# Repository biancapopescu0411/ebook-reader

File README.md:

# README - OpenBook

**OpenBook** este un sistem portabil pentru citirea cărților electronice, proiectat în jurul microcontrollerului ESP32-C6-WROOM-1-N8. Dispozitivul integrează o serie de componente inteligente pentru stocare, afișare, alimentare și comunicații, toate optimizate pentru eficiență energetică și portabilitate.

## Diagrama bloc

---

## Componente Hardware & Funcționalitate
### Microcontroller Principal
- **ESP32-C6-WROOM-1-N8**

- Procesor RISC-V 32-bit

- Conectivitate Wi-Fi 6 și Bluetooth 5.0

- Memorie Flash internă de 8MB

- Nivel logic și alimentare: 3.3V

- Responsabil de comunicarea cu senzorii, ecranul EPD, memoria externă și stocarea datelor.

---

## Interfețe de Comunicație

| Interfață | Componente Conectate |
|----------|-----------------------|
| **I2C**  | BME688, MAX17048, DS3231SN |
| **SPI**  | Display E-Ink, SD Card, Flash Memory |
| **UART** | Serial debug via USB-C (TX/RX) |
| **GPIO** | Butoane, LED-uri, semnale control |

---

## Energie și Alimentare

- Alimentare prin **USB-C** sau baterie **Li-Po**
- Condensatori de decuplare de **100nF** aproape de fiecare pin de alimentare
- Regulator **LDO 3.3V** pentru circuitele logice
- Încărcarea bateriei este gestionată de **MCP73831**
- Plan de masă aplicat pe ambele straturi (**TOP & BOTTOM**) pentru stabilitate electrică

---

## Funcționalitate Detaliată

### ESP32-C6
- Rol: procesor central, interfațare completă cu toate modulele
- Conectat direct la:
  - UART: comunicare cu e-Paper
  - SPI: display, stocare date
  - I2C: senzori și RTC

### Display E-Ink
- Afișare text/imagine cu consum redus
- Interfață SPI dedicată

### Baterie & Protecții
- Baterie conectată la 4 pad-uri pentru economie de spațiu
- Decuplare prin condensatori de 100nF
- Protecții plasate strategic prin via stitching

---

## Structura Proiect
```
├── Hardware
│   ├── schematic_final.sch            # Fișier schematic
│   └── pcb final.brd            # Fișier PCB
├── Manufacturing
│   ├── gerbers.zip             # Fișiere Gerber generate
│   ├── bom.csv            # Bill of Materials
│   └── Pick and place.csv           # Pick and Place file
├── Mechanical
│   ├── exploded.step  # Model 3D exploded (PCB + baterie + ecran + carcasă)
│   └── OpenBook Enclosure.f3z  # Model nativ Fusion360
├── Images
│   ├── 3d.png
│   └── baterie.png
|   └── exploded view.png
|   └── no lid.png
|   └── openbook enclosure.png
|   └── screen view.png
|   └── screen.png
└── README.md
```

## Bill of Materials
| Componenta | Link | Datasheet |
|-----------|--------------|-----------|
| BUTTON | [Model](https://industry.panasonic.com/global/en/products/control/switch/light-touch/number/evqpuj02k) | [Datasheet](https://www.lcsc.com/datasheet/lcsc_datasheet_2201121800_PANASONIC-EVQPUJ02K_C2936858.pdf) |
| CAPACITOR | [Model](https://componentsearchengine.com/part-view/R0402%201%25%20100%20K%20(RC0402FR-07100KL)/YAGEO) | [Datasheet](//efaidnbmnnnibpcajpcglclefindmkaj/https://www.resistor.com/assets/pdf/0402tstd.pdf) |
| CPH3225A | [Model](https://www.snapeda.com/parts/CPH3225A/Seiko+Instruments/view-part/?ref=eda) | [Datasheet](https://octopart.com/datasheet/cph3225a-seiko-25340571) |
| EVQPUJ02K | [Model](https://industry.panasonic.com/global/en/products/control/switch/light-touch/number/evqpuj02k) | [Datasheet](https://www.lcsc.com/datasheet/lcsc_datasheet_2201121800_PANASONIC-EVQPUJ02K_C2936858.pdf) |
| KP-1608SURCK | [Model](https://www.snapeda.com/parts/KP-1608SURCK/Kingbright/view-part/?ref=search&t=LED%200603) | [Datasheet](//efaidnbmnnnibpcajpcglclefindmkaj/https://media.elv.com/file/107153_led_surck1608_data.pdf) |
| USBLC6-2SC6Y | [Model](https://www.snapeda.com/parts/USBLC6-2SC6Y/STMicroelectronics/view-part/?ref=eda) | [Datasheet](https://www.digikey.com/en/htmldatasheets/production/1375342/0/0/1/usblc6-2sc6y) |
| SD0805S020S1R0 | [Model](https://ro.mouser.com/ProductDetail/KYOCERA-AVX/SD0805S020S1R0?qs=jCA%252BPfw4LHbpkAoSnwrdjw%3D%3D) | [Datasheet](https://www.alldatasheet.com/view.jsp?Searchword=SD0805S&sField=2) |
| PGB1010603MR | [Model](https://www.snapeda.com/parts/PGB1010603MR/Littelfuse/view-part/?ref=eda) | [Datasheet](https://www.alldatasheet.com/view.jsp?Searchword=Pgb1010603mr&gad_source=1&gbraid=0AAAAADcdDU8aYfZtfJfdZ9I5j6RwZ_cbA&gclid=Cj0KCQjwqcO_BhDaARIsACz62vOPBOBe0eOh5gDUFkkKl4JBcbmoFZYtJ8BOnbaWqr_BuUCcVWvbutAaAmGkEALw_wcB) |
| BD5229G-TR  | [Model](https://componentsearchengine.com/part-view/BD5229G-TR/ROHM%20Semiconductor) | [Datasheet](https://www.lcsc.com/datasheet/lcsc_datasheet_2201131330_ROHM-Semicon-BD5229G-TR_C962636.pdf) |
| XC6220A331MR-G | [Model](https://componentsearchengine.com/part-view/XC6220A331MR-G/Torex) | [Datasheet](https://www.alldatasheet.com/view.jsp?Searchword=Xc6220&gad_source=1&gbraid=0AAAAADcdDU8aYfZtfJfdZ9I5j6RwZ_cbA&gclid=Cj0KCQjwqcO_BhDaARIsACz62vPS06NB6tLgniZzfaVpKNu1m811BNk6AEPfg4DbP6f5S8QWA_pW_UQaAv-0EALw_wcB) |
| XC6220A331MR-G | [Model](https://componentsearchengine.com/part-view/XC6220A331MR-G/Torex) | [Datasheet](https://www.alldatasheet.com/view.jsp?Searchword=Xc6220&gad_source=1&gbraid=0AAAAADcdDU8aYfZtfJfdZ9I5j6RwZ_cbA&gclid=Cj0KCQjwqcO_BhDaARIsACz62vMO5_aHsn35cIZBK6oCFuB_WOxz_zKu4yOHJ69-EnaUd5Jfas_Avm8aAuk5EALw_wcB) |
| USB4110-GF-A  | [Model](https://componentsearchengine.com/part-view/USB4110-GF-A/GCT%20(GLOBAL%20CONNECTOR%20TECHNOLOGY)) | [Datasheet](//efaidnbmnnnibpcajpcglclefindmkaj/https://gct.co/files/drawings/usb4110.pdf) |
| Adafruit | [Model](https://eu.mouser.com/ProductDetail/Adafruit/4208?qs=PzGy0jfpSMtbScLbr0L5dw%3D%3D) | [Datasheet](https://www.arrow.com/en/manufacturers/adafruit-industries/datasheets) |
| Bobina | [Model](https://store.comet.srl.ro/Catalogue/Product/43497/) | [Datasheet](https://www.scribd.com/document/814581278/Datasheet-Bobina) |
| PFMF | [Model](https://www.mouser.co.uk/ProductDetail/EPCOS-TDK/B72520T0350K062?qs=dEfas%2FXlABIszF52uu7vrg%3D%3D) | [Datasheet](https://ro.mouser.com/c/ds/circuit-protection/thermistors/resettable-fuses-pptc/?m=Schurter&series=PFMF) |
| DMG2305UX-7 | [Model](https://componentsearchengine.com/part-view/DMG2305UX-7/Diodes%20Incorporated) | [Datasheet](//efaidnbmnnnibpcajpcglclefindmkaj/https://www.mouser.com/datasheet/2/115/DMG2305UX-266242.pdf?srsltid=AfmBOop22k34YTJJra1xubiU6LPiN4M4JlcWbRoSNdxSGFak8uWgXPpK) |
| Si1308EDL-T1-GE3 | [Model](https://componentsearchengine.com/part-view/SI1308EDL-T1-GE3/Vishay) | [Datasheet](https://www.alldatasheet.com/view.jsp?Searchword=Si1308edl&gad_source=1&gbraid=0AAAAADcdDU-px713ONYSnQ2O-gcwqYcFq&gclid=Cj0KCQjwqcO_BhDaARIsACz62vN_Nz3MJOc6J_03gnVBm7aSqC8v9wyP0VD-iRKP-gFrYgdhLi99I14aAlVJEALw_wcB) |
| R0402 | [Model](https://componentsearchengine.com/part-view/R0402%201%25%20100%20K%20(RC0402FR-07100KL)/YAGEO) | [Datasheet](//efaidnbmnnnibpcajpcglclefindmkaj/https://www.resistor.com/assets/pdf/0402tstd.pdf) |
| BME680 | [Model](https://www.snapeda.com/parts/BME680/Bosch/view-part/?welcome=home) | [Datasheet](//efaidnbmnnnibpcajpcglclefindmkaj/https://www.bosch-sensortec.com/media/boschsensortec/downloads/datasheets/bst-bme680-ds001.pdf) |
| SMD Solder | [Model](https://grabcad.com/library/solder-jumpers-1) | [Datasheet]() |
| W25Q512JVEIQ | [Model](https://www.snapeda.com/parts/ESP32-C6-WROOM-1-N8/Espressif+Systems/view-part/?ref=eda) | [Datasheet](//efaidnbmnnnibpcajpcglclefindmkaj/https://www.mouser.com/datasheet/2/949/W25Q512JV_SPI_RevB_06252019_KMS-2487502.pdf?srsltid=AfmBOoquExqDVgxEELF9CzuOGxHos0CD1nQDROHD6Eebdm2foNzqozqU) |
| ESP32-C6-WROOM-1-N8 | [Model](https://www.snapeda.com/parts/ESP32-C6-WROOM-1-N8/Espressif+Systems/view-part/?ref=eda) | [Datasheet](//efaidnbmnnnibpcajpcglclefindmkaj/https://www.mouser.com/catalog/specsheets/Espressif_ESP32_C6_WROOM_1%20_Datasheet_V0.1_PRELIMINARY_en.pdf?srsltid=AfmBOooHQKNitqODRaaPjoZInfWKTacDER1t5uRK6sKqT13TrzvVo_B7) |
| DS3231SN# | [Model](https://www.snapeda.com/parts/DS3231SN%23/Analog+Devices/view-part/?ref=eda) | [Datasheet](https://www.alldatasheet.com/view.jsp?Searchword=Ds3231sn%20datasheet&gad_source=1&gbraid=0AAAAADcdDU-Gy9URfMxGmqiPg7ci5L3wR&gclid=Cj0KCQjwqcO_BhDaARIsACz62vMkK3ETSnW2w7mo0Fa-wgWJGn89AxWCyIND6k5X8MmoPl6hv6VWwT8aAiS-EALw_wcB) |
| MAX17048G+T10 | [Model](https://www.snapeda.com/parts/MAX17048G+T10/Analog+Devices/view-part/?ref=eda) | [Datasheet](https://www.alldatasheet.com/view.jsp?Searchword=Max17048&gad_source=1&gbraid=0AAAAADcdDU8aYfZtfJfdZ9I5j6RwZ_cbA&gclid=Cj0KCQjwqcO_BhDaARIsACz62vNa9xrVfzjCjADRwXD0RBbo4Nret3ywwteDGLJKZui8ZL8KdVlTE7caAvQxEALw_wcB) |
| MCP73831T-5ACI/OT | [Model](https://www.mouser.co.uk/ProductDetail/Microchip-Technology/MCP73831T-5ACI-OT?qs=hH%252BOa0VZEiAcgAcEkuamXg%3D%3D) | [Datasheet](//efaidnbmnnnibpcajpcglclefindmkaj/https://ww1.microchip.com/downloads/en/DeviceDoc/MCP73831-Family-Data-Sheet-DS20001984H.pdf) |

## Detaliere Pini Utilizați (ESP32-C6 / U2)

| Pin ESP32 | Funcție Principală                  | Componentă Conectată / Scop                  |
| :-------- | :---------------------------------- | :------------------------------------------- |
| IO3       | RESET                               | SW2, IC5                                     |
| IO5       | GPIO                                | J4 (EPD_DC)                                  |
| IO6       | SPI SCK                             | J4 (EPD_SCK), J3 (SD_CLK)                    |
| IO7       | SPI MOSI                            | J4 (EPD_DIN), J3 (SD_DI)                     |
| IO8       | BOOT                                | SW1 (Buton Boot)                             |
| IO10      | GPIO / SPI CS                       | J3 (SD_CS)                                   |
| IO11      | GPIO / SPI CS                       | J4 (EPD_CS)                                  |
| IO13      | USB D-                              | J2 (USB-C D-) via D2                         |
| IO14      | USB D+                              | J2 (USB-C D+) via D2                         |
| IO19      | I2C SDA                             | IC2 (RTC SDA), IC3 (BME SDA/SDO)             |
| IO20      | I2C SCL                             | IC2 (RTC SCL), IC3 (BME SCL/SCK)             |
| IO21      | GPIO                                | J4 (EPD_RST)                                 |
| IO26      | GPIO                                | J4 (EPD_BUSY)                                |
| IO27      | SPI MISO                            | J4 (EPD_DOUT), J3 (SD_DO)                    |
| EN        | Enable                              | Pull-up la 3.3V                              |
| VDD       | Power                               | 3.3V                                         |
| GND       | Ground                              | Ground                                       |
| IO12      | Neutilizat                          | -                                            |
| IO24      | Neutilizat                          | -                                            |
| IO25      | Neutilizat                          | -                                            |

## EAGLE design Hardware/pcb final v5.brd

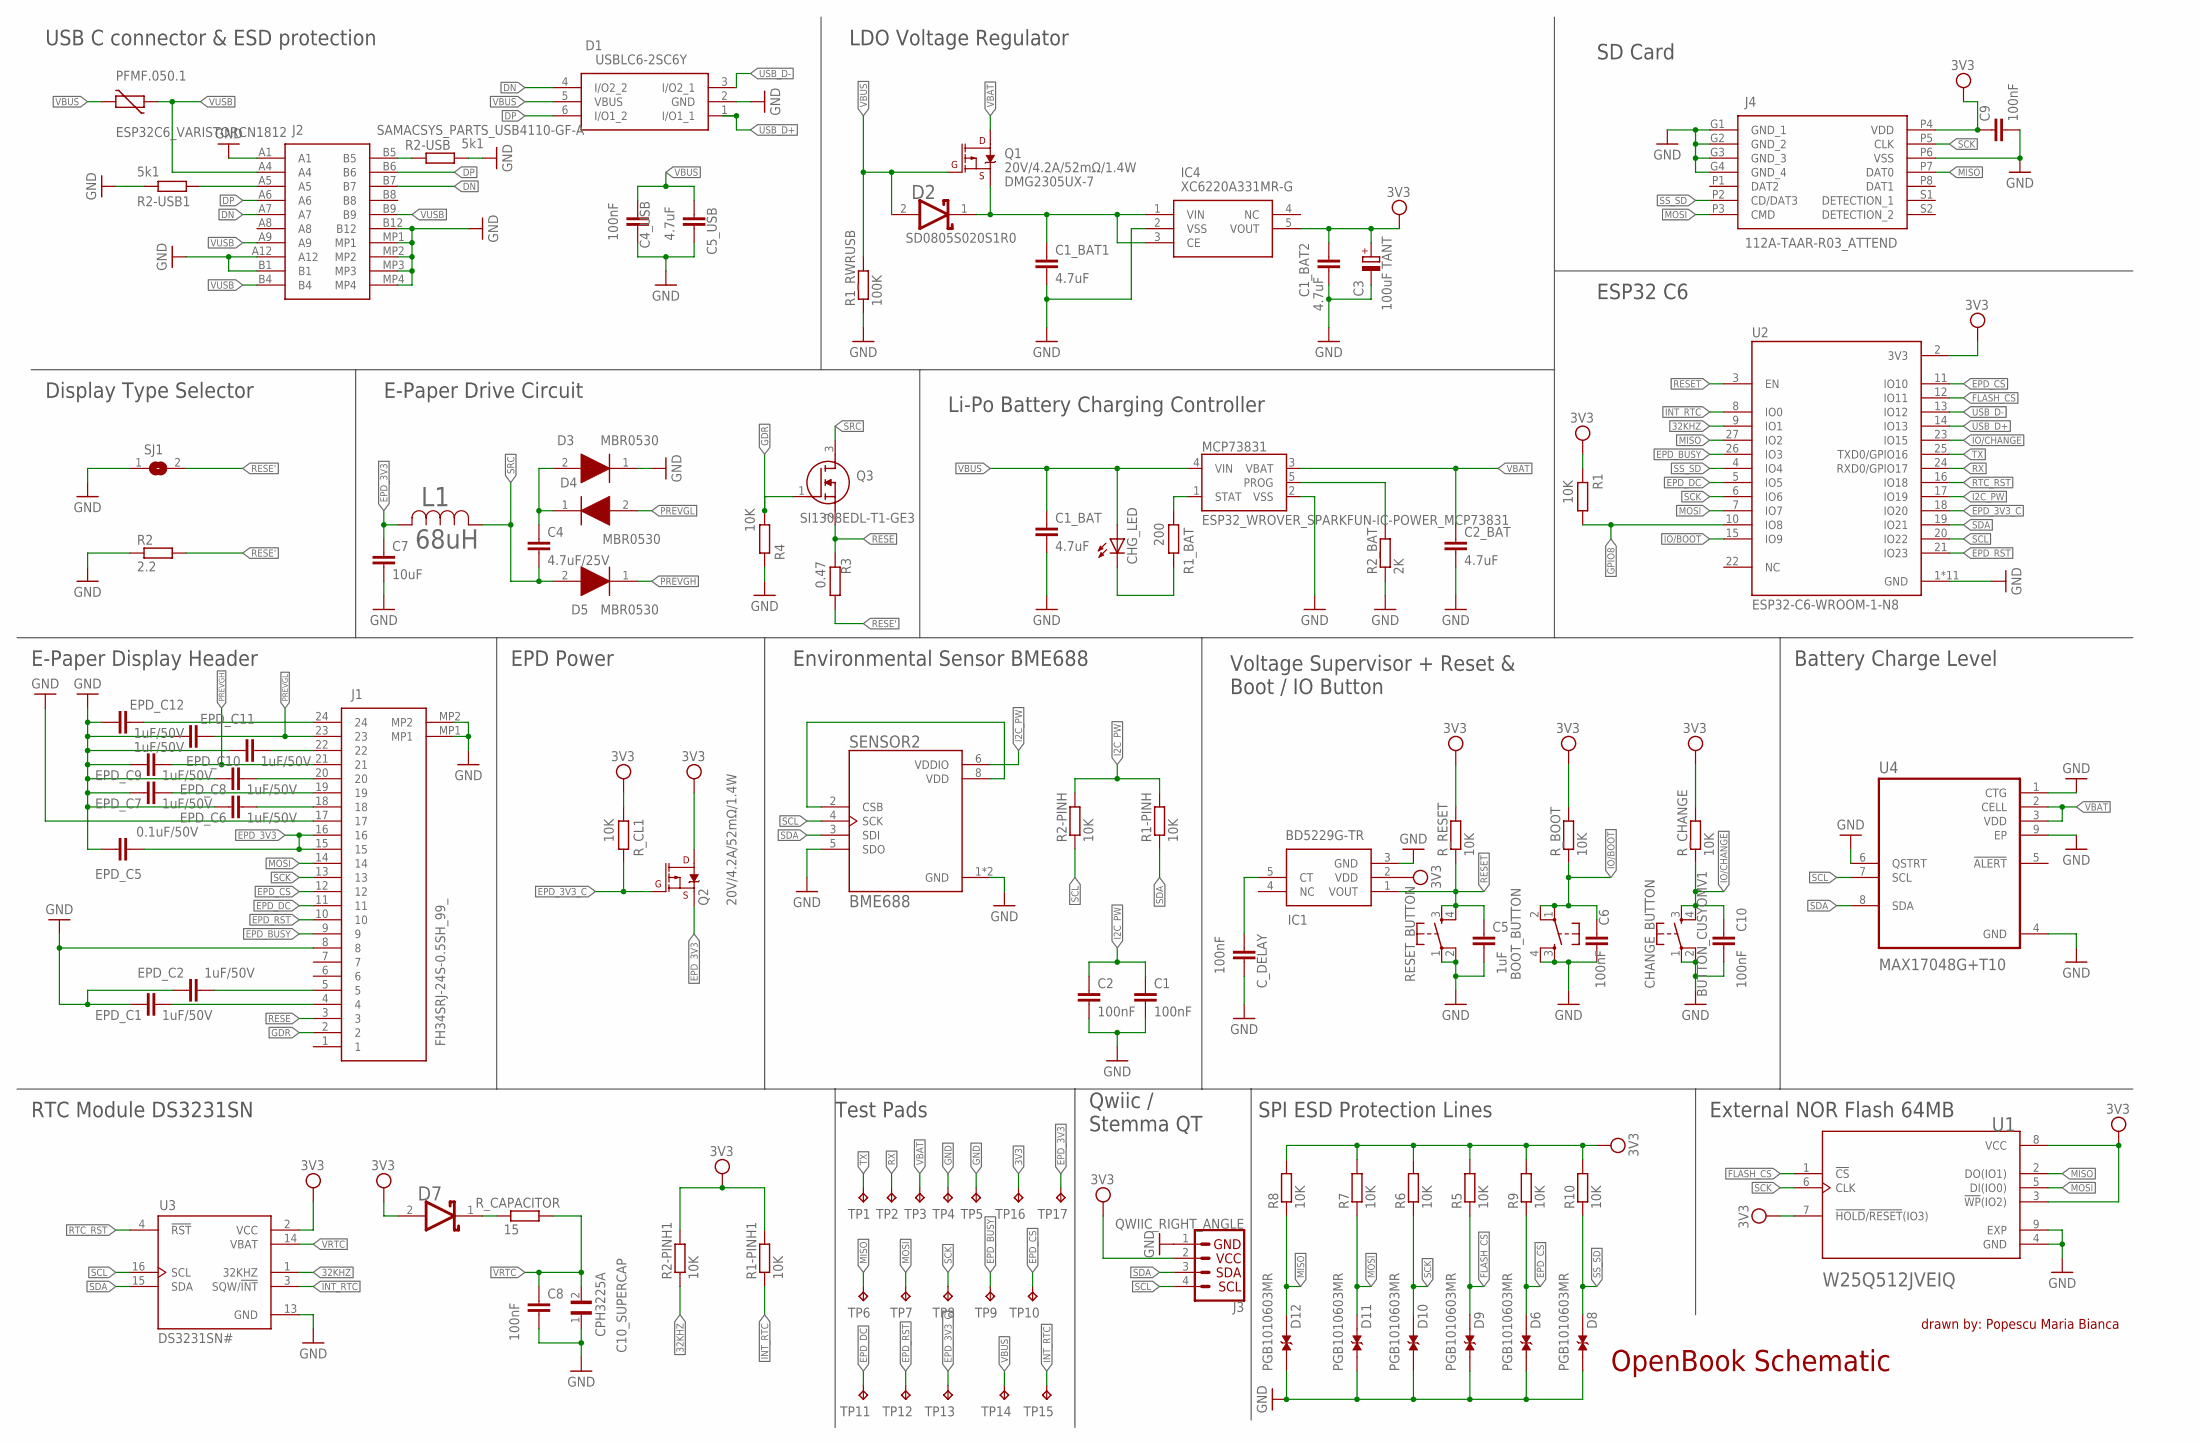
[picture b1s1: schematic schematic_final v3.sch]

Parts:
BOOT_BUTTON: BUTTON_CUSYOMV1; MYBUTTON
C1, C2, C4_USB, C6, C8, C9, C10: 100nF; EAGLE-LTSPICE_C0402
C1_BAT, C1_BAT1, C1_BAT2, C2_BAT, C5_USB: 4.7uF; EAGLE-LTSPICE_C0402
C3: 100uF TANT; RCL_CT3528
C4: 4.7uF/25V; EAGLE-LTSPICE_C0402
C5: 1uF; EAGLE-LTSPICE_C0402
C7: 10uF; EAGLE-LTSPICE_C0402
C10_SUPERCAP: CPH3225A; CAPCP3225X100N
CHANGE_BUTTON: BUTTON_CUSYOMV1; MYBUTTON
CHG_LED: ADAFRUIT_LEDCHIP-LED0603; ADAFRUIT_CHIP-LED0603
C_DELAY: 100nF; EAGLE-LTSPICE_C0402
D1: USBLC6-2SC6Y; SOT95P280X145-6N
D2: SD0805S020S1R0; ESP32_WROVER_AVX---SD0805S020S1R0_AVX_SD0805S020S1R0_0
D3, D4, D5: MBR0530; SOD3716X135N
D6, D8, D9, D10, D11, D12: PGB1010603MR; DIOC1608X36N
D7: ESP32_WROVER_AVX---SD0805S020S1R0_AVX_SD0805S020S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; ESP32_WROVER_AVX---SD0805S020S1R0_AVX_SD0805S020S1R0_0
EPD_C1, EPD_C2, EPD_C6, EPD_C7, EPD_C8, EPD_C9, EPD_C10, EPD_C11, EPD_C12: 1uF/50V; EAGLE-LTSPICE_C0402
EPD_C5: 0.1uF/50V; EAGLE-LTSPICE_C0402
IC1: BD5229G-TR; SOT95P280X125-5N
IC4: XC6220A331MR-G; SOT95P280X120-5N
J1: FH34SRJ-24S-0.5SH_99_; FH34SRJ24S05SH99
J2: SAMACSYS_PARTS_USB4110-GF-A; SAMACSYS_PARTS_USB4110GFA
J3: QWIIC_RIGHT_ANGLE; JST04_1MM_RA
J4: 112A-TAAR-R03_ATTEND; 112ATAARR03ATTEND
L1: 68uH; IND_4828-WE-TPC_WRE
MCP73831: ESP32_WROVER_SPARKFUN-IC-POWER_MCP73831; ESP32_WROVER_SPARKFUN-IC-POWER_SOT23-5
PFMF.050.1: ESP32C6_VARISTORCN1812; ESP32C6_VARISTOR_CT/CN1812
Q1, Q2: 20V/4.2A/52mΩ/1.4W; ESP32_WROVER_SPARKFUN-DISCRETESEMI_SOT23-3
Q3: SI1308EDL-T1-GE3; SOT65P210X110-3N
R1, R1-PINH, R1-PINH1, R2-PINH, R2-PINH1, R4, R5, R6, R7, R8, R9, R10: 10K; ESP32_WROVER_EAGLE-LTSPICE_R0402
R1_BAT: 200; ESP32_WROVER_EAGLE-LTSPICE_R0402
R1_RWRUSB: 100K; ESP32_WROVER_EAGLE-LTSPICE_R0402
R2: 2.2; ESP32_WROVER_EAGLE-LTSPICE_R0402
R2-USB, R2-USB1: 5k1; ESP32_WROVER_EAGLE-LTSPICE_R0402
R2_BAT: 2K; ESP32_WROVER_EAGLE-LTSPICE_R0402
R3: 0.47; ESP32_WROVER_EAGLE-LTSPICE_R0402
RESET_BUTTON: RESET_BUTTON; MYBUTTON
R_BOOT: 10K; ESP32_WROVER_EAGLE-LTSPICE_R0402
R_CAPACITOR: 15; ESP32_WROVER_EAGLE-LTSPICE_R0402
R_CHANGE: 10K; ESP32_WROVER_EAGLE-LTSPICE_R0402
R_CL1: 10K; ESP32_WROVER_EAGLE-LTSPICE_R0402
R_RESET: 10K; ESP32_WROVER_EAGLE-LTSPICE_R0402
SENSOR2: BME688; ESP32_WROVER_BME680_PSON80P300X300X100-8N
SJ1: SJ
TP1, TP2, TP3, TP4, TP5, TP6, TP7, TP8, TP9, TP10, TP11, TP12, TP13, TP14, TP15, TP16, TP17: TPTP20R; TP20R
U1: W25Q512JVEIQ; SON127P600X800X80-9N
U2: ESP32-C6-WROOM-1-N8; XCVR_ESP32-C6-WROOM-1-N8
U3: DS3231SN#; SOIC127P1032X265-16N
U4: MAX17048G+T10; SON50P200X200X80-9N

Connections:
3V3: C1_BAT2.1, C3.+, C9.1, D7.2 (ANODE), IC1.2 (VDD), IC4.5 (VOUT), J3.2, J4.P4 (VDD), Q2.3 (D), R1.2, R1-PINH1.2, R2-PINH1.2, R5.2, R6.2, R7.2, R8.2, R9.2, R10.2, R_BOOT.2, R_CHANGE.2, R_CL1.2, R_RESET.2, TP16.TP, U1.3 (!WP!(IO2)), U1.7 (!HOLD!/!RESET!(IO3)), U1.8 (VCC), U2.2 (3V3), U3.2 (VCC)
32KHZ: R2-PINH1.1, U2.9 (IO1), U3.1 (32KHZ)
DN: D1.4 (I/O2_2), J2.A7, J2.B7
DP: D1.6 (I/O1_2), J2.A6, J2.B6
EPD_3V3: C7.1, EPD_C5.2, J1.15, J1.16, L1.2, Q2.2 (S), TP17.TP
EPD_3V3_C: Q2.1 (G), R_CL1.1, TP13.TP, U2.18 (IO20)
EPD_BUSY: J1.9, TP9.TP, U2.26 (IO3)
EPD_CS: D6.2, J1.12, R9.1, TP10.TP, U2.11 (IO10)
EPD_DC: J1.11, TP11.TP, U2.5 (IO5)
EPD_RST: J1.10, TP12.TP, U2.21 (IO23)
FLASH_CS: D9.2, R5.1, U1.1 (!CS), U2.12 (IO11)
GDR: J1.2, Q3.1 (G), R4.2
GND: BOOT_BUTTON.3, BOOT_BUTTON.4, C1.2, C1_BAT.2, C1_BAT1.2, C1_BAT2.2, C2.2, C2_BAT.2, C3.-, C4_USB.2, C5.2, C5_USB.2, C6.2, C7.2, C8.2, C9.2, C10.2, C10_SUPERCAP.1, CHANGE_BUTTON.1, CHANGE_BUTTON.2, C_DELAY.2, D1.2 (GND), D3.1 (K), D6.1, D8.1, D9.1, D10.1, D11.1, D12.1, EPD_C1.1, EPD_C2.1, EPD_C5.1, EPD_C6.1, EPD_C7.1, EPD_C8.1, EPD_C9.1, EPD_C10.1, EPD_C11.1, EPD_C12.1, IC1.3 (GND), IC4.2 (VSS), J1.8, J1.17, J1.MP1, J1.MP2, J2.A1, J2.A12, J2.B1, J2.B12, J2.MP1, J2.MP2, J2.MP3, J2.MP4, J3.1, J4.G1 (GND_1), J4.G2 (GND_2), J4.G3 (GND_3), J4.G4 (GND_4), J4.P6 (VSS), MCP73831.2 (VSS), R1_RWRUSB.1, R2.1, R2-USB.2, R2-USB1.1, R2_BAT.1, R4.1, RESET_BUTTON.1, RESET_BUTTON.2, SENSOR2.1 (GND), SENSOR2.5 (SDO), SENSOR2.7 (GND), SJ1.1, TP4.TP, TP5.TP, U1.4 (GND), U1.9 (EXP), U2.1 (GND), U2.28 (GND), U2.29_1 (GND), U2.29_2 (GND), U2.29_3 (GND), U2.29_4 (GND), U2.29_5 (GND), U2.29_6 (GND), U2.29_7 (GND), U2.29_8 (GND), U2.29_9 (GND), U3.13 (GND), U4.1 (CTG), U4.4 (GND), U4.6 (QSTRT), U4.9 (EP)
GPIO8: R1.1, U2.10 (IO8)
I2C_PW: C1.1, C2.1, R1-PINH.2, R2-PINH.2, SENSOR2.6 (VDDIO), U2.17 (IO19)
INT_RTC: R1-PINH1.1, TP15.TP, U2.8 (IO0), U3.3 (SQW/!INT)
IO/BOOT: BOOT_BUTTON.1, BOOT_BUTTON.2, C6.1, R_BOOT.1, U2.15 (IO9)
IO/CHANGE: C10.1, CHANGE_BUTTON.3, CHANGE_BUTTON.4, R_CHANGE.1, U2.23 (IO15)
MISO: D12.2, J4.P7 (DAT0), R8.1, TP6.TP, U1.2 (DO(IO1)), U2.27 (IO2)
MOSI: D11.2, J1.14, J4.P3 (CMD), R7.1, TP7.TP, U1.5 (DI(IO0)), U2.7 (IO7)
unnamed: J2.A5, R2-USB1.2
unnamed: J2.B5, R2-USB.1
unnamed: SENSOR2.2 (CSB), SENSOR2.8 (VDD)
unnamed: C1_BAT1.1, D2.1 (CATHODE), IC4.1 (VIN), IC4.3 (CE), Q1.2 (S)
unnamed: D2.2 (ANODE), Q1.1 (G), R1_RWRUSB.2
unnamed: C4.1, D3.2 (A), D4.1 (K)
unnamed: MCP73831.1 (STAT), R1_BAT.2
unnamed: CHG_LED.C, R1_BAT.1
unnamed: MCP73831.5 (PROG), R2_BAT.2
unnamed: EPD_C2.2, J1.5
unnamed: EPD_C12.2, J1.24
unnamed: EPD_C1.2, J1.4
unnamed: EPD_C10.2, J1.22
unnamed: EPD_C8.2, J1.20
unnamed: EPD_C7.2, J1.19
unnamed: EPD_C6.2, J1.18
unnamed: C_DELAY.1, IC1.5 (CT)
unnamed: D7.1 (CATHODE), R_CAPACITOR.1
PREVGH: D5.1 (K), EPD_C9.2, J1.21
PREVGL: D4.2 (A), EPD_C11.2, J1.23
RESE: J1.3, Q3.2 (S), R3.2
RESE': R2.2, R3.1, SJ1.2
RESET: C5.1, IC1.1 (VOUT), RESET_BUTTON.3, RESET_BUTTON.4, R_RESET.1, U2.3 (EN)
RTC_RST: U2.16 (IO18), U3.4 (!RST)
RX: TP2.TP, U2.24 (RXD0/GPIO17)
SCK: D10.2, J1.13, J4.P5 (CLK), R6.1, TP8.TP, U1.6 (CLK), U2.6 (IO6)
SCL: J3.4, R2-PINH.1, SENSOR2.4 (SCK), U2.20 (IO22), U3.16 (SCL), U4.7 (SCL)
SDA: J3.3, R1-PINH.1, SENSOR2.3 (SDI), U2.19 (IO21), U3.15 (SDA), U4.8 (SDA)
SRC: C4.2, D5.2 (A), L1.1, Q3.3 (D)
SS_SD: D8.2, J4.P2 (CD/DAT3), R10.1, U2.4 (IO4)
TX: TP1.TP, U2.25 (TXD0/GPIO16)
USB_D+: D1.1 (I/O1_1), U2.14 (IO13)
USB_D-: D1.3 (I/O2_1), U2.13 (IO12)
VBAT: C2_BAT.1, MCP73831.3 (VBAT), Q1.3 (D), TP3.TP, U4.2 (CELL), U4.3 (VDD)
VBUS: C1_BAT.1, C4_USB.1, C5_USB.1, CHG_LED.A, D1.5 (VBUS), MCP73831.4 (VIN), PFMF.050.1.2, TP14.TP
VRTC: C8.1, C10_SUPERCAP.2, R_CAPACITOR.2, U3.14 (VBAT)
VUSB: J2.A4, J2.A9, J2.B4, J2.B9, PFMF.050.1.1

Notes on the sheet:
OpenBook Schematic
drawn by: Popescu Maria Bianca
USB C connector & ESD protection
LDO Voltage Regulator
SD Card
ESP32 C6
Li-Po Battery Charging Controller
E-Paper Drive Circuit
Display Type Selector
E-Paper Display Header
EPD Power
Environmental Sensor BME688
Voltage Supervisor + Reset & Boot / IO Button
Battery Charge Level
External NOR Flash 64MB
SPI ESD Protection Lines
Qwiic / Stemma QT
Test Pads
RTC Module DS3231SN

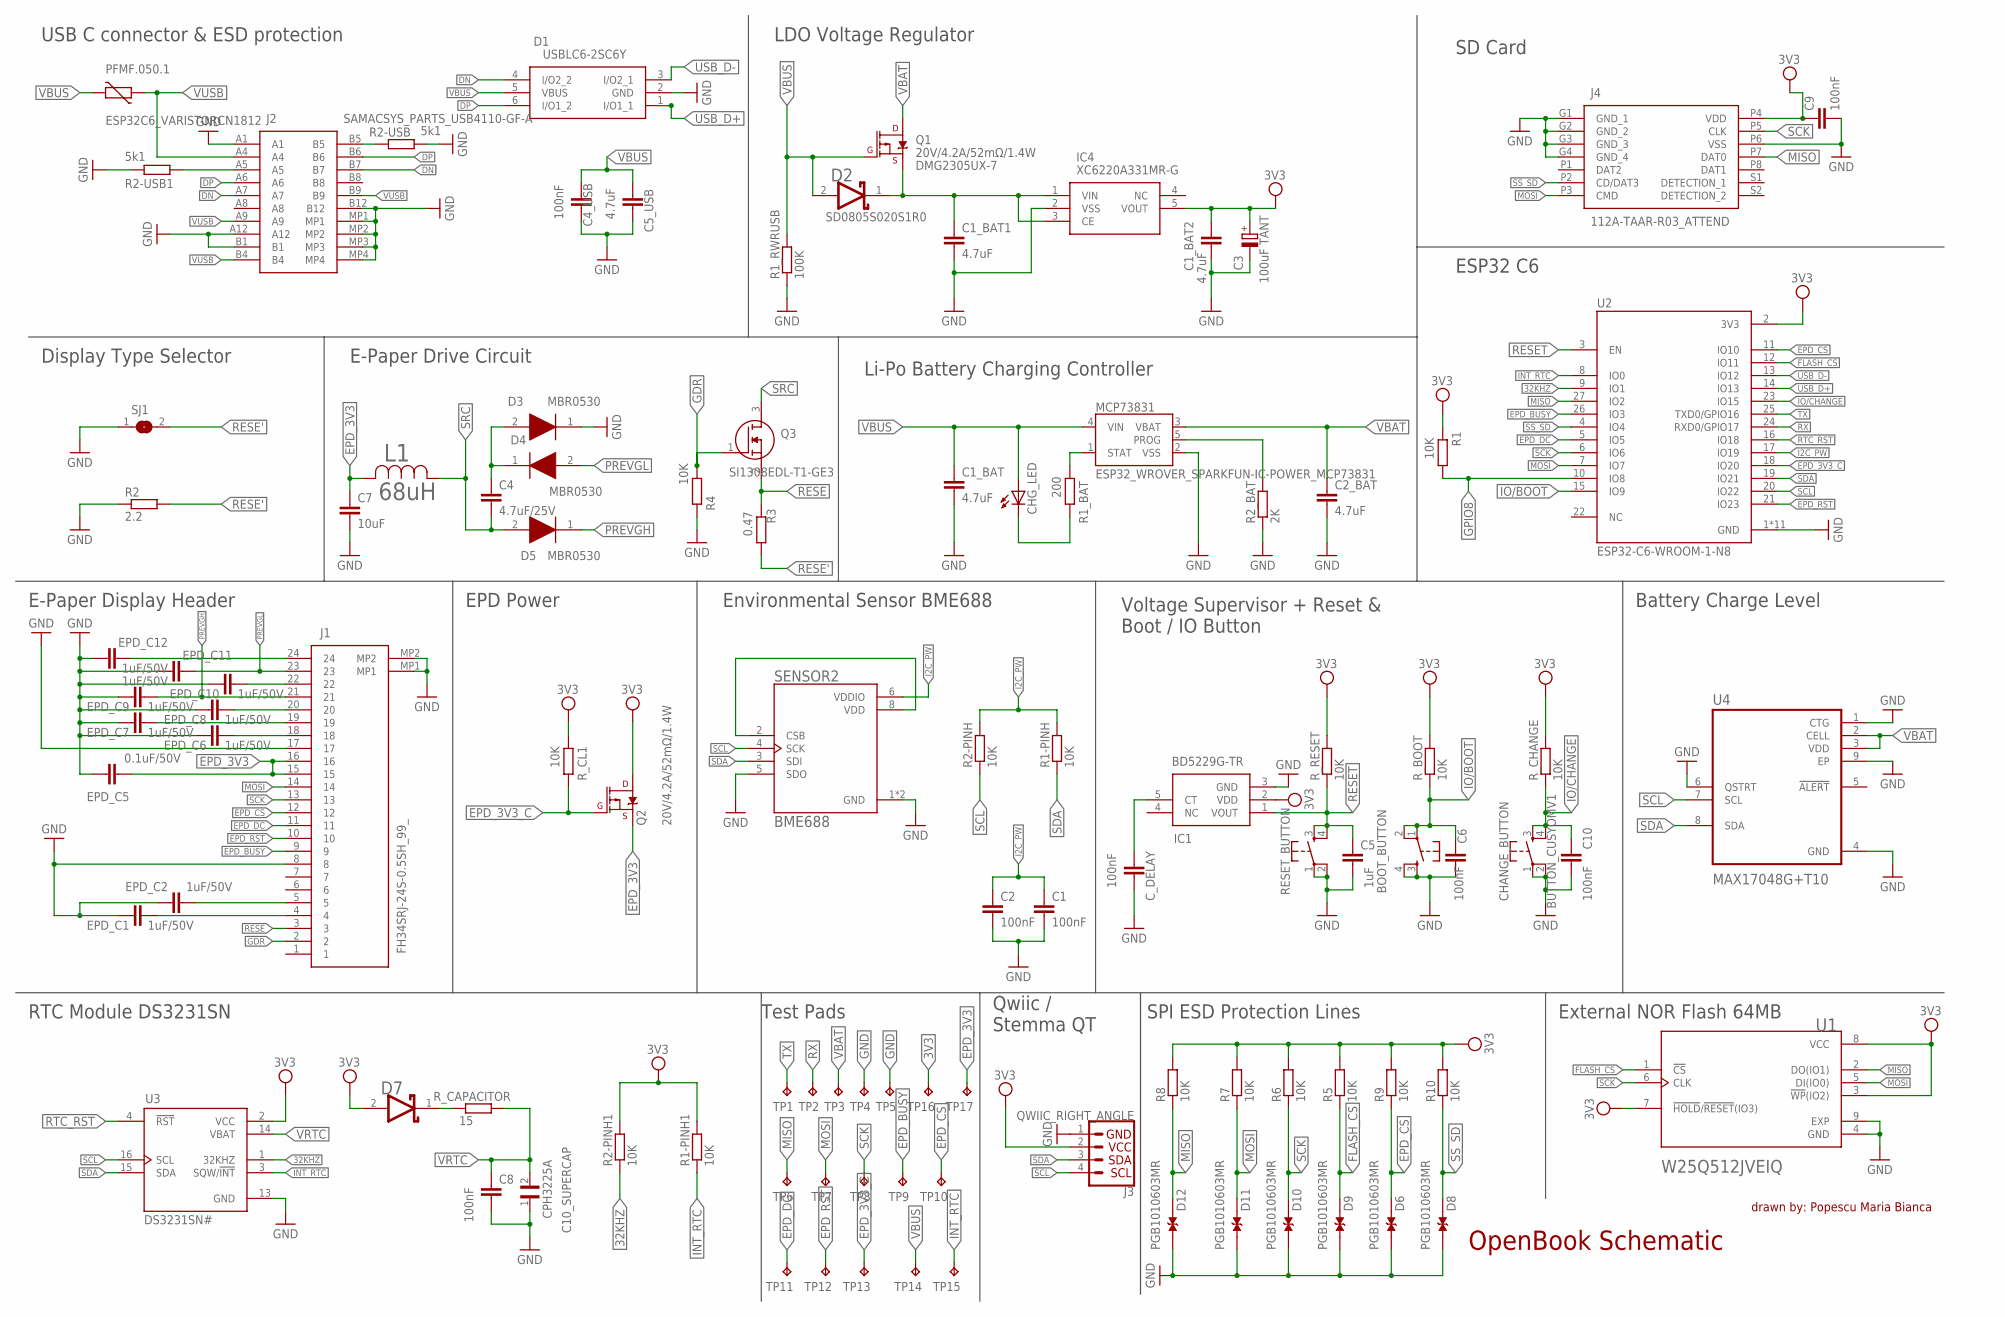
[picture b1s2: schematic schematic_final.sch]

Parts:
BOOT_BUTTON: BUTTON_CUSYOMV1; MYBUTTON
C1, C2, C4_USB, C6, C8, C9, C10: 100nF; EAGLE-LTSPICE_C0402
C1_BAT, C1_BAT1, C1_BAT2, C2_BAT, C5_USB: 4.7uF; EAGLE-LTSPICE_C0402
C3: 100uF TANT; RCL_CT3528
C4: 4.7uF/25V; EAGLE-LTSPICE_C0402
C5: 1uF; EAGLE-LTSPICE_C0402
C7: 10uF; EAGLE-LTSPICE_C0402
C10_SUPERCAP: CPH3225A; CAPCP3225X100N
CHANGE_BUTTON: BUTTON_CUSYOMV1; MYBUTTON
CHG_LED: ADAFRUIT_LEDCHIP-LED0603; ADAFRUIT_CHIP-LED0603
C_DELAY: 100nF; EAGLE-LTSPICE_C0402
D1: USBLC6-2SC6Y; SOT95P280X145-6N
D2: SD0805S020S1R0; ESP32_WROVER_AVX---SD0805S020S1R0_AVX_SD0805S020S1R0_0
D3, D4, D5: MBR0530; SOD3716X135N
D6, D8, D9, D10, D11, D12: PGB1010603MR; DIOC1608X36N
D7: ESP32_WROVER_AVX---SD0805S020S1R0_AVX_SD0805S020S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; ESP32_WROVER_AVX---SD0805S020S1R0_AVX_SD0805S020S1R0_0
EPD_C1, EPD_C2, EPD_C6, EPD_C7, EPD_C8, EPD_C9, EPD_C10, EPD_C11, EPD_C12: 1uF/50V; EAGLE-LTSPICE_C0402
EPD_C5: 0.1uF/50V; EAGLE-LTSPICE_C0402
IC1: BD5229G-TR; SOT95P280X125-5N
IC4: XC6220A331MR-G; SOT95P280X120-5N
J1: FH34SRJ-24S-0.5SH_99_; FH34SRJ24S05SH99
J2: SAMACSYS_PARTS_USB4110-GF-A; SAMACSYS_PARTS_USB4110GFA
J3: QWIIC_RIGHT_ANGLE; JST04_1MM_RA
J4: 112A-TAAR-R03_ATTEND; 112ATAARR03ATTEND
L1: 68uH; IND_4828-WE-TPC_WRE
MCP73831: ESP32_WROVER_SPARKFUN-IC-POWER_MCP73831; ESP32_WROVER_SPARKFUN-IC-POWER_SOT23-5
PFMF.050.1: ESP32C6_VARISTORCN1812; ESP32C6_VARISTOR_CT/CN1812
Q1, Q2: 20V/4.2A/52mΩ/1.4W; ESP32_WROVER_SPARKFUN-DISCRETESEMI_SOT23-3
Q3: SI1308EDL-T1-GE3; SOT65P210X110-3N
R1, R1-PINH, R1-PINH1, R2-PINH, R2-PINH1, R4, R5, R6, R7, R8, R9, R10: 10K; ESP32_WROVER_EAGLE-LTSPICE_R0402
R1_BAT: 200; ESP32_WROVER_EAGLE-LTSPICE_R0402
R1_RWRUSB: 100K; ESP32_WROVER_EAGLE-LTSPICE_R0402
R2: 2.2; ESP32_WROVER_EAGLE-LTSPICE_R0402
R2-USB, R2-USB1: 5k1; ESP32_WROVER_EAGLE-LTSPICE_R0402
R2_BAT: 2K; ESP32_WROVER_EAGLE-LTSPICE_R0402
R3: 0.47; ESP32_WROVER_EAGLE-LTSPICE_R0402
RESET_BUTTON: RESET_BUTTON; MYBUTTON
R_BOOT: 10K; ESP32_WROVER_EAGLE-LTSPICE_R0402
R_CAPACITOR: 15; ESP32_WROVER_EAGLE-LTSPICE_R0402
R_CHANGE: 10K; ESP32_WROVER_EAGLE-LTSPICE_R0402
R_CL1: 10K; ESP32_WROVER_EAGLE-LTSPICE_R0402
R_RESET: 10K; ESP32_WROVER_EAGLE-LTSPICE_R0402
SENSOR2: BME688; ESP32_WROVER_BME680_PSON80P300X300X100-8N
SJ1: SJ
TP1, TP2, TP3, TP4, TP5, TP6, TP7, TP8, TP9, TP10, TP11, TP12, TP13, TP14, TP15, TP16, TP17: TPTP20R; TP20R
U1: W25Q512JVEIQ; SON127P600X800X80-9N
U2: ESP32-C6-WROOM-1-N8; XCVR_ESP32-C6-WROOM-1-N8
U3: DS3231SN#; SOIC127P1032X265-16N
U4: MAX17048G+T10; SON50P200X200X80-9N

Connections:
3V3: C1_BAT2.1, C3.+, C9.1, D7.2 (ANODE), IC1.2 (VDD), IC4.5 (VOUT), J3.2, J4.P4 (VDD), Q2.3 (D), R1.2, R1-PINH1.2, R2-PINH1.2, R5.2, R6.2, R7.2, R8.2, R9.2, R10.2, R_BOOT.2, R_CHANGE.2, R_CL1.2, R_RESET.2, TP16.TP, U1.3 (!WP!(IO2)), U1.7 (!HOLD!/!RESET!(IO3)), U1.8 (VCC), U2.2 (3V3), U3.2 (VCC)
32KHZ: R2-PINH1.1, U2.9 (IO1), U3.1 (32KHZ)
DN: D1.4 (I/O2_2), J2.A7, J2.B7
DP: D1.6 (I/O1_2), J2.A6, J2.B6
EPD_3V3: C7.1, EPD_C5.2, J1.15, J1.16, L1.2, Q2.2 (S), TP17.TP
EPD_3V3_C: Q2.1 (G), R_CL1.1, TP13.TP, U2.18 (IO20)
EPD_BUSY: J1.9, TP9.TP, U2.26 (IO3)
EPD_CS: D6.2, J1.12, R9.1, TP10.TP, U2.11 (IO10)
EPD_DC: J1.11, TP11.TP, U2.5 (IO5)
EPD_RST: J1.10, TP12.TP, U2.21 (IO23)
FLASH_CS: D9.2, R5.1, U1.1 (!CS), U2.12 (IO11)
GDR: J1.2, Q3.1 (G), R4.2
GND: BOOT_BUTTON.3, BOOT_BUTTON.4, C1.2, C1_BAT.2, C1_BAT1.2, C1_BAT2.2, C2.2, C2_BAT.2, C3.-, C4_USB.2, C5.2, C5_USB.2, C6.2, C7.2, C8.2, C9.2, C10.2, C10_SUPERCAP.1, CHANGE_BUTTON.1, CHANGE_BUTTON.2, C_DELAY.2, D1.2 (GND), D3.1 (K), D6.1, D8.1, D9.1, D10.1, D11.1, D12.1, EPD_C1.1, EPD_C2.1, EPD_C5.1, EPD_C6.1, EPD_C7.1, EPD_C8.1, EPD_C9.1, EPD_C10.1, EPD_C11.1, EPD_C12.1, IC1.3 (GND), IC4.2 (VSS), J1.8, J1.17, J1.MP1, J1.MP2, J2.A1, J2.A12, J2.B1, J2.B12, J2.MP1, J2.MP2, J2.MP3, J2.MP4, J3.1, J4.G1 (GND_1), J4.G2 (GND_2), J4.G3 (GND_3), J4.G4 (GND_4), J4.P6 (VSS), MCP73831.2 (VSS), R1_RWRUSB.1, R2.1, R2-USB.2, R2-USB1.1, R2_BAT.1, R4.1, RESET_BUTTON.1, RESET_BUTTON.2, SENSOR2.1 (GND), SENSOR2.5 (SDO), SENSOR2.7 (GND), SJ1.1, TP4.TP, TP5.TP, U1.4 (GND), U1.9 (EXP), U2.1 (GND), U2.28 (GND), U2.29_1 (GND), U2.29_2 (GND), U2.29_3 (GND), U2.29_4 (GND), U2.29_5 (GND), U2.29_6 (GND), U2.29_7 (GND), U2.29_8 (GND), U2.29_9 (GND), U3.13 (GND), U4.1 (CTG), U4.4 (GND), U4.6 (QSTRT), U4.9 (EP)
GPIO8: R1.1, U2.10 (IO8)
I2C_PW: C1.1, C2.1, R1-PINH.2, R2-PINH.2, SENSOR2.6 (VDDIO), U2.17 (IO19)
INT_RTC: R1-PINH1.1, TP15.TP, U2.8 (IO0), U3.3 (SQW/!INT)
IO/BOOT: BOOT_BUTTON.1, BOOT_BUTTON.2, C6.1, R_BOOT.1, U2.15 (IO9)
IO/CHANGE: C10.1, CHANGE_BUTTON.3, CHANGE_BUTTON.4, R_CHANGE.1, U2.23 (IO15)
MISO: D12.2, J4.P7 (DAT0), R8.1, TP6.TP, U1.2 (DO(IO1)), U2.27 (IO2)
MOSI: D11.2, J1.14, J4.P3 (CMD), R7.1, TP7.TP, U1.5 (DI(IO0)), U2.7 (IO7)
unnamed: J2.A5, R2-USB1.2
unnamed: J2.B5, R2-USB.1
unnamed: SENSOR2.2 (CSB), SENSOR2.8 (VDD)
unnamed: C1_BAT1.1, D2.1 (CATHODE), IC4.1 (VIN), IC4.3 (CE), Q1.2 (S)
unnamed: D2.2 (ANODE), Q1.1 (G), R1_RWRUSB.2
unnamed: C4.1, D3.2 (A), D4.1 (K)
unnamed: MCP73831.1 (STAT), R1_BAT.2
unnamed: CHG_LED.C, R1_BAT.1
unnamed: MCP73831.5 (PROG), R2_BAT.2
unnamed: EPD_C2.2, J1.5
unnamed: EPD_C12.2, J1.24
unnamed: EPD_C1.2, J1.4
unnamed: EPD_C10.2, J1.22
unnamed: EPD_C8.2, J1.20
unnamed: EPD_C7.2, J1.19
unnamed: EPD_C6.2, J1.18
unnamed: C_DELAY.1, IC1.5 (CT)
unnamed: D7.1 (CATHODE), R_CAPACITOR.1
PREVGH: D5.1 (K), EPD_C9.2, J1.21
PREVGL: D4.2 (A), EPD_C11.2, J1.23
RESE: J1.3, Q3.2 (S), R3.2
RESE': R2.2, R3.1, SJ1.2
RESET: C5.1, IC1.1 (VOUT), RESET_BUTTON.3, RESET_BUTTON.4, R_RESET.1, U2.3 (EN)
RTC_RST: U2.16 (IO18), U3.4 (!RST)
RX: TP2.TP, U2.24 (RXD0/GPIO17)
SCK: D10.2, J1.13, J4.P5 (CLK), R6.1, TP8.TP, U1.6 (CLK), U2.6 (IO6)
SCL: J3.4, R2-PINH.1, SENSOR2.4 (SCK), U2.20 (IO22), U3.16 (SCL), U4.7 (SCL)
SDA: J3.3, R1-PINH.1, SENSOR2.3 (SDI), U2.19 (IO21), U3.15 (SDA), U4.8 (SDA)
SRC: C4.2, D5.2 (A), L1.1, Q3.3 (D)
SS_SD: D8.2, J4.P2 (CD/DAT3), R10.1, U2.4 (IO4)
TX: TP1.TP, U2.25 (TXD0/GPIO16)
USB_D+: D1.1 (I/O1_1), U2.14 (IO13)
USB_D-: D1.3 (I/O2_1), U2.13 (IO12)
VBAT: C2_BAT.1, MCP73831.3 (VBAT), Q1.3 (D), TP3.TP, U4.2 (CELL), U4.3 (VDD)
VBUS: C1_BAT.1, C4_USB.1, C5_USB.1, CHG_LED.A, D1.5 (VBUS), MCP73831.4 (VIN), PFMF.050.1.2, TP14.TP
VRTC: C8.1, C10_SUPERCAP.2, R_CAPACITOR.2, U3.14 (VBAT)
VUSB: J2.A4, J2.A9, J2.B4, J2.B9, PFMF.050.1.1

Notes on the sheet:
OpenBook Schematic
drawn by: Popescu Maria Bianca
USB C connector & ESD protection
LDO Voltage Regulator
SD Card
ESP32 C6
Li-Po Battery Charging Controller
E-Paper Drive Circuit
Display Type Selector
E-Paper Display Header
EPD Power
Environmental Sensor BME688
Voltage Supervisor + Reset & Boot / IO Button
Battery Charge Level
External NOR Flash 64MB
SPI ESD Protection Lines
Qwiic / Stemma QT
Test Pads
RTC Module DS3231SN

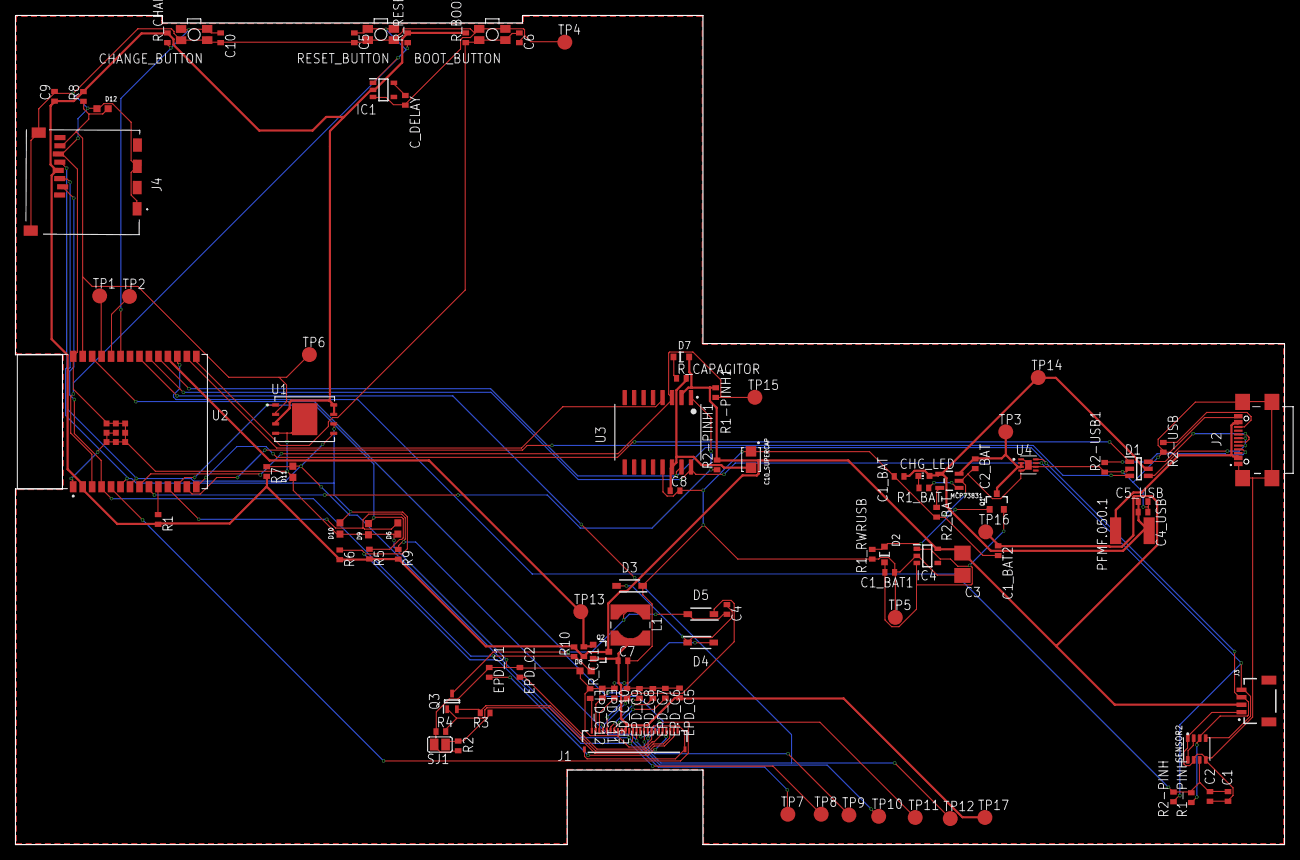
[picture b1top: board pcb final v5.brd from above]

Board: 2 copper layers, 170.2 x 111.2 mm, 103 parts (0 on the bottom side), 57 nets.

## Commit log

2025-04-04 Create LICENSE
2025-04-05 added project
2025-04-15 resolved issues

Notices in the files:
parts and their libraries:
COPYRIGHT: Copyright (C) 2024 Ultra Librarian. All rights reserved.
